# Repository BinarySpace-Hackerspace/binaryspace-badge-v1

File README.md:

# binaryspace-badge-v1
BinarySpace pcb badge for members - V1

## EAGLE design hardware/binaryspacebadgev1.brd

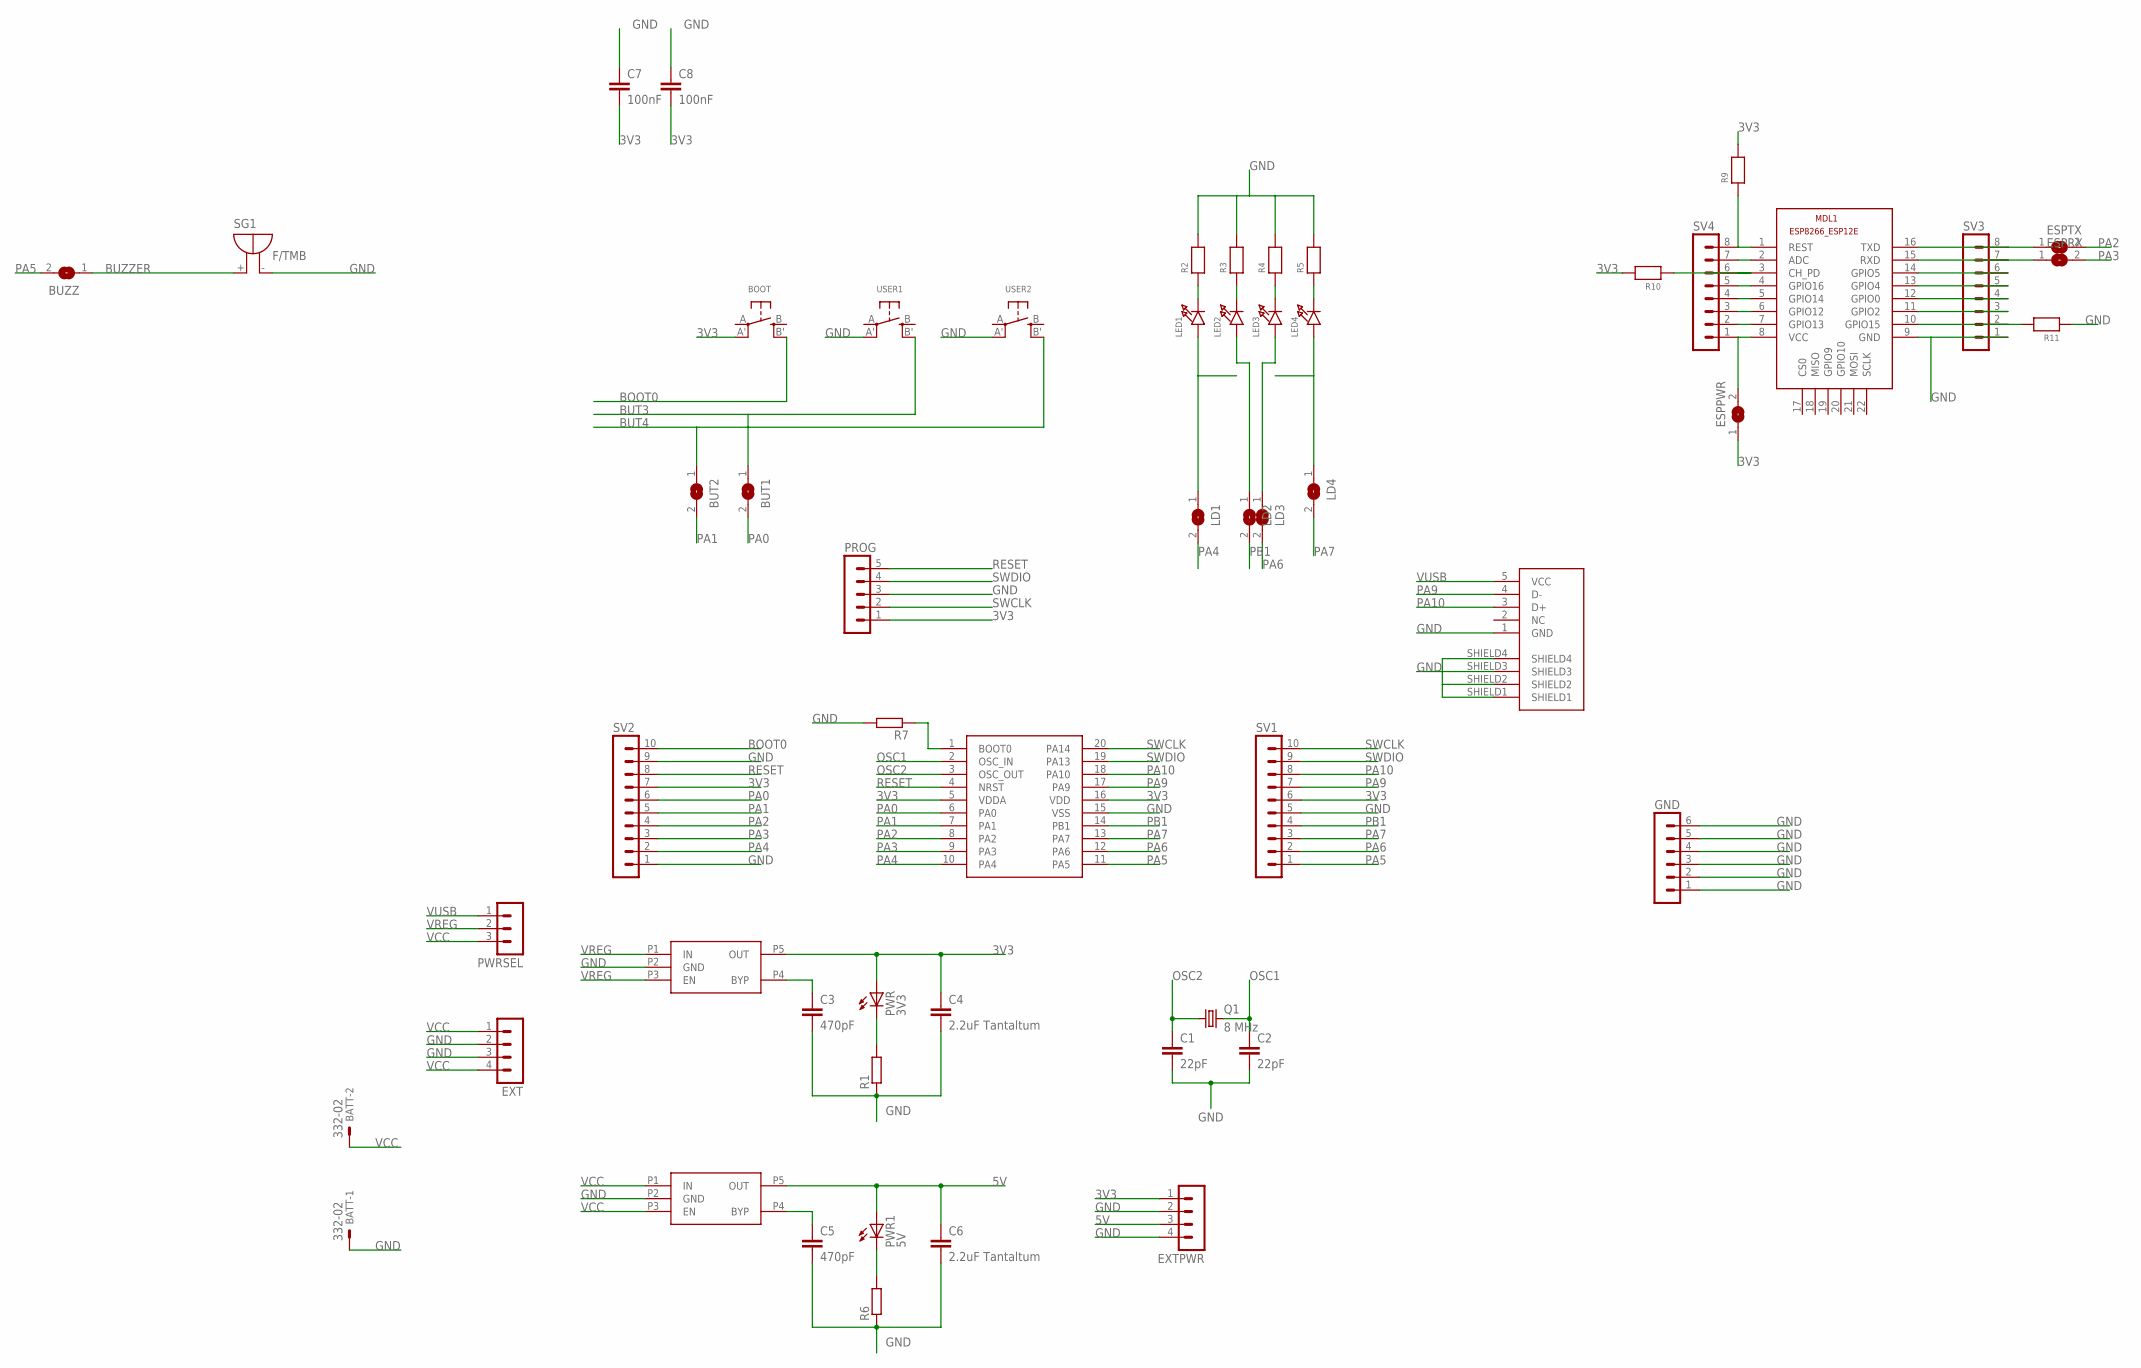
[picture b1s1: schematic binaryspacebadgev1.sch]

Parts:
BATT: 332-02
BOOT: SWITCH_TACT_SMT; EVQ-Q2
BUT1, BUT2: SOLDERJUMPER; SOLDERJUMPER_ARROW_NOPASTE
BUZZ: SOLDERJUMPER; SOLDERJUMPER_ARROW_NOPASTE
C1, C2: 22pF; C0603
C3, C5: 470pF; C0603
C4, C6: 2.2uF Tantaltum; C0805
C7, C8: 100nF; C0603
ESPPWR: SOLDERJUMPER; SOLDERJUMPER_ARROW_NOPASTE
ESPRX: SOLDERJUMPER; SOLDERJUMPER_ARROW_NOPASTE
ESPTX: SOLDERJUMPER; SOLDERJUMPER_ARROW_NOPASTE
EXT: MA04-1
EXTPWR: MA04-1
GND: MA06-1
LD1, LD2, LD3, LD4: SOLDERJUMPER; SOLDERJUMPER_ARROW_NOPASTE
LED1, LED2, LED3, LED4: LED0805; CHIPLED_0805
MDL1: ESP8266-12EESP8266-ESP12E; ESP8266-ESP12E
PROG: MA05-1
PWR: 3V3; SML0603
PWR1: 5V; SML0603
PWRSEL: MA03-1
Q1: 8 MHz; SM49
R1, R6, R7: R-EU_R0603; R0603
R2, R3, R4, R5, R9, R10, R11: RESISTOR0603; 0603
SG1: F/TMB
SV1, SV2: MA10-1
SV3, SV4: MA08-1
U$1: STM32F030X4792-5925; TSSOP20
U$2, U$4: MIC5219-X.XBM5MIC5219-3.3YM5TR; SOT-23-5
U$3: USBSOCK_MINI_SMD
USER1, USER2: SWITCH_TACT_SMT; EVQ-Q2

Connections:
3V3: BOOT.A' (P1), C4.1, C7.2, C8.2, ESPPWR.1, EXTPWR.1, PROG.1, PWR.A, R9.2, R10.2, SV1.6, SV2.7, U$1.5 (VDDA), U$1.16 (VDD), U$2.P5 (OUT)
5V: C6.1, EXTPWR.3, PWR1.A, U$4.P5 (OUT)
BLAH: PWR1.C, R6.2
BLAH2: PWR.C, R1.2
BOOT0: BOOT.B' (S1), R7.1, SV2.10, U$1.1 (BOOT0)
BUT3: BUT1.1, USER1.B' (S1)
BUT4: BUT2.1, USER2.B' (S1)
BUZZER: BUZZ.1, SG1.+
GND: BATT.1, C1.2, C2.2, C3.2, C4.2, C5.2, C6.2, C7.1, C8.1, EXT.2, EXT.3, EXTPWR.2, EXTPWR.4, GND.1, GND.2, GND.3, GND.4, GND.5, GND.6, MDL1.9 (GND), PROG.3, R1.1, R2.2, R3.2, R4.2, R5.2, R6.1, R7.2, R11.1, SG1.-, SV1.5, SV2.1, SV2.9, SV3.1, U$1.15 (VSS), U$2.P2 (GND), U$3.1 (GND), U$3.SHIELD1, U$3.SHIELD2, U$3.SHIELD3, U$3.SHIELD4, U$4.P2 (GND), USER1.A' (P1), USER2.A' (P1)
LED1: LD1.1, LED1.A
LED2: LD2.1, LED2.A
LED3: LD3.1, LED3.A
LED4: LD4.1, LED4.A
unnamed: C3.1, U$2.P4 (BYP)
unnamed: C5.1, U$4.P4 (BYP)
unnamed: LED1.C, R2.1
unnamed: LED2.C, R3.1
unnamed: LED3.C, R4.1
unnamed: LED4.C, R5.1
unnamed: ESPTX.1, MDL1.16 (TXD), SV3.8
unnamed: ESPRX.1, MDL1.15 (RXD), SV3.7
unnamed: MDL1.14 (GPIO5), SV3.6
unnamed: MDL1.13 (GPIO4), SV3.5
unnamed: MDL1.12 (GPIO0), SV3.4
unnamed: MDL1.11 (GPIO2), SV3.3
unnamed: MDL1.10 (GPIO15), R11.2, SV3.2
unnamed: MDL1.1 (REST), R9.1, SV4.8
unnamed: MDL1.2 (ADC), SV4.7
unnamed: MDL1.3 (CH_PD), R10.1, SV4.6
unnamed: MDL1.4 (GPIO16), SV4.5
unnamed: MDL1.5 (GPIO14), SV4.4
unnamed: MDL1.6 (GPIO12), SV4.3
unnamed: MDL1.7 (GPIO13), SV4.2
unnamed: ESPPWR.2, MDL1.8 (VCC), SV4.1
OSC1: C2.1, Q1.2, U$1.2 (OSC_IN)
OSC2: C1.1, Q1.1, U$1.3 (OSC_OUT)
PA0: BUT1.2, SV2.6, U$1.6 (PA0)
PA1: BUT2.2, SV2.5, U$1.7 (PA1)
PA2: ESPTX.2, SV2.4, U$1.8 (PA2)
PA3: ESPRX.2, SV2.3, U$1.9 (PA3)
PA4: LD1.2, SV2.2, U$1.10 (PA4)
PA5: BUZZ.2, SV1.1, U$1.11 (PA5)
PA6: LD3.2, SV1.2, U$1.12 (PA6)
PA7: LD4.2, SV1.3, U$1.13 (PA7)
PA9: SV1.7, U$1.17 (PA9), U$3.4 (D-)
PA10: SV1.8, U$1.18 (PA10), U$3.3 (D+)
PB1: LD2.2, SV1.4, U$1.14 (PB1)
RESET: PROG.5, SV2.8, U$1.4 (NRST)
SWCLK: PROG.2, SV1.10, U$1.20 (PA14)
SWDIO: PROG.4, SV1.9, U$1.19 (PA13)
VCC: BATT.2, EXT.1, EXT.4, PWRSEL.3, U$4.P1 (IN), U$4.P3 (EN)
VREG: PWRSEL.2, U$2.P1 (IN), U$2.P3 (EN)
VUSB: PWRSEL.1, U$3.5 (VCC)

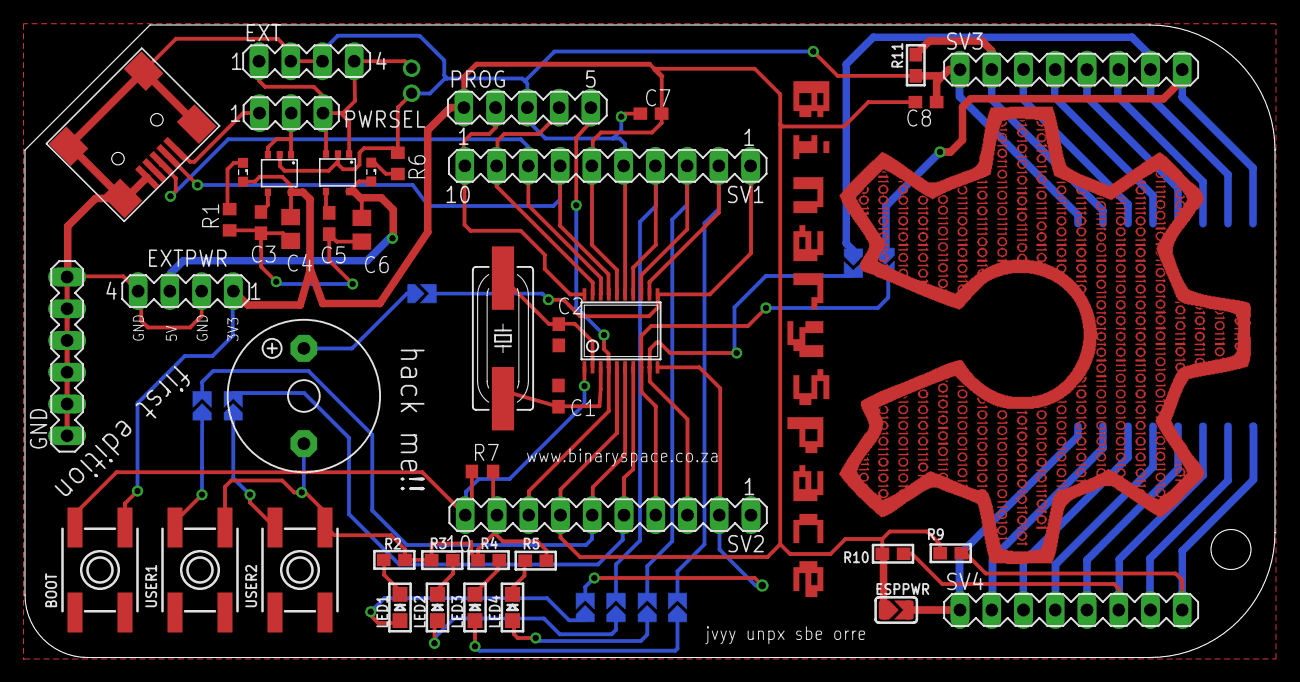
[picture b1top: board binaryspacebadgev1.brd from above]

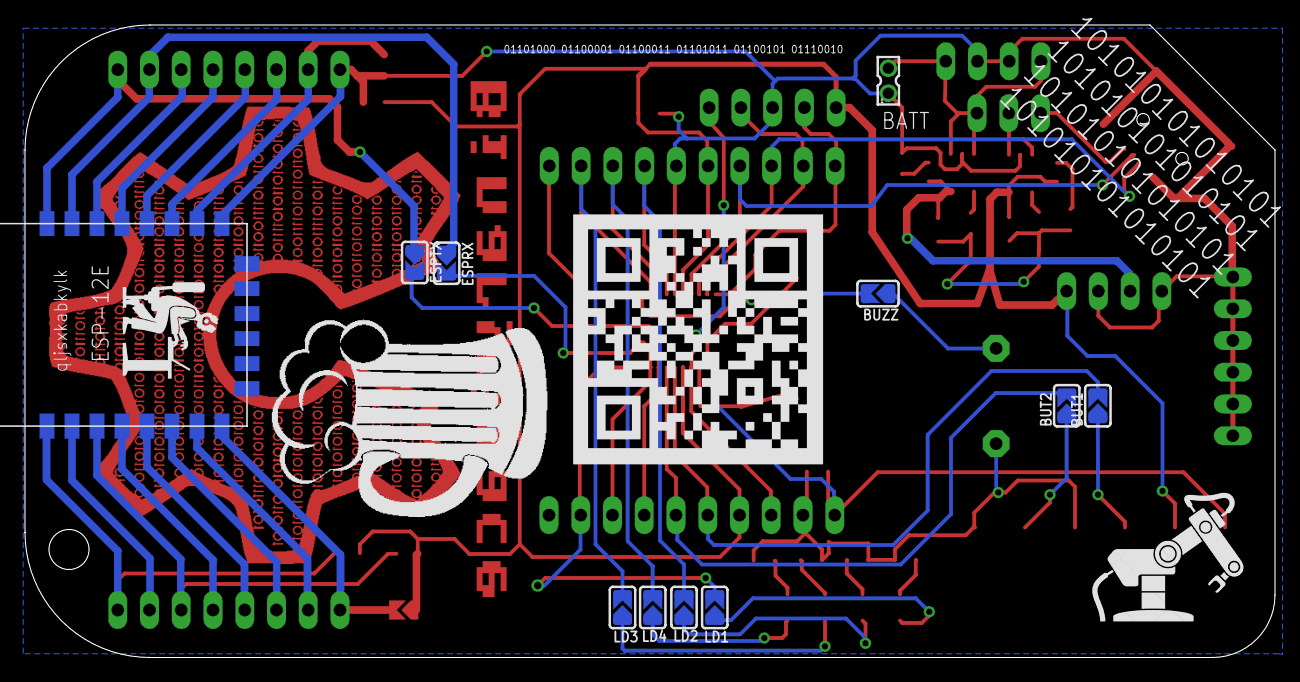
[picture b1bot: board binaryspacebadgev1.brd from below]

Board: 2 copper layers, 100.0 x 50.6 mm, 54 parts (11 on the bottom side), 53 nets.

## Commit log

2016-04-08 added design files

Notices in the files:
parts and their libraries:
microbuilder: This work is placed in the public domain, and may be freely used for commercial and non-commercial work with the following conditions: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
